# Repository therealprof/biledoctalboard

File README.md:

# BiLEDOctalBoard

## About This Project

# Octal LED board (bi-directional)

I just saw a nice project on [Hackaday](https://hackaday.com/2018/09/08/see-binary-on-your-breadboard/) which provides a common anode or cathode 8 LED display for breadboarding. Since it is horizontally mounted bridging over two breadboards (which I find a quite weird layout but okay) it takes a lot of space while providing rather little functionality. So I came up with my own board which mounts vertically offers space for 8 or 16 LEDs (your choice) in antiparallel configuration (technically you could also use this for multiplexing 2x8 LEDs) which means that if you connect hook up ground to one end and Vcc to the other end (which depends on the direction the LEDs are mounted so I didn&#39;t silkscreen any) either the upper or the lower LED (or none if the according pin is floating) will light up so.

## Renderings

### Top

### Bottom

## BOM

|Count|Component|Details|Datasheet|
|-|-|-|-|
|x||||

---

This project is managed and available on

You can view it [here](https://aisler.net/p/RDFTEKUD). Start your own Powerful Prototype on [here](https://aisler.net).

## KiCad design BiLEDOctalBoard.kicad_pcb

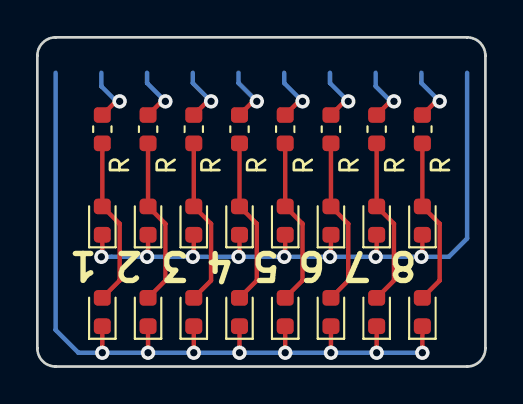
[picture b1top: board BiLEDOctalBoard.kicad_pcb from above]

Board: 2 copper layers, 24.9 x 18.3 mm, 25 parts (1 on the bottom side), 18 nets.

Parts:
D1, D2, D3, D4, D5, D6, D7, D8, D9, D10, D11, D12, D13, D14, D15, D16: LED; LED_0603_1608Metric
J1: Conn_01x10_Male; Harwin_M20-89010xx_1x10_P2.54mm_Horizontal
R: R; R_0603_1608Metric
R#2, R#3, R#4, R#5, R#6, R#7, R#8: R; R_0603_1608Metric

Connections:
unnamed: D1.1, D3.1, D5.1, D7.1, D9.1, D11.1, D13.1, D15.1, J1.10
unnamed: D1.2, D2.2, R.2
unnamed: D3.2, D4.2, R#5.2
unnamed: D5.2, D6.2, R#2.2
unnamed: D7.2, D8.2, R#6.2
unnamed: D2.1, D4.1, D6.1, D8.1, D10.1, D12.1, D14.1, D16.1, J1.1
unnamed: D9.2, D10.2, R#3.2
unnamed: D11.2, D12.2, R#7.2
unnamed: D13.2, D14.2, R#4.2
unnamed: D15.2, D16.2, R#8.2
unnamed: J1.2, R#8.1
unnamed: J1.3, R#4.1
unnamed: J1.4, R#7.1
unnamed: J1.5, R#3.1
unnamed: J1.6, R#6.1
unnamed: J1.7, R#2.1
unnamed: J1.8, R#5.1
unnamed: J1.9, R.1

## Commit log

2018-09-09 Syncing AISLER project with GitHub repository
2018-09-09 Added Kicad files
